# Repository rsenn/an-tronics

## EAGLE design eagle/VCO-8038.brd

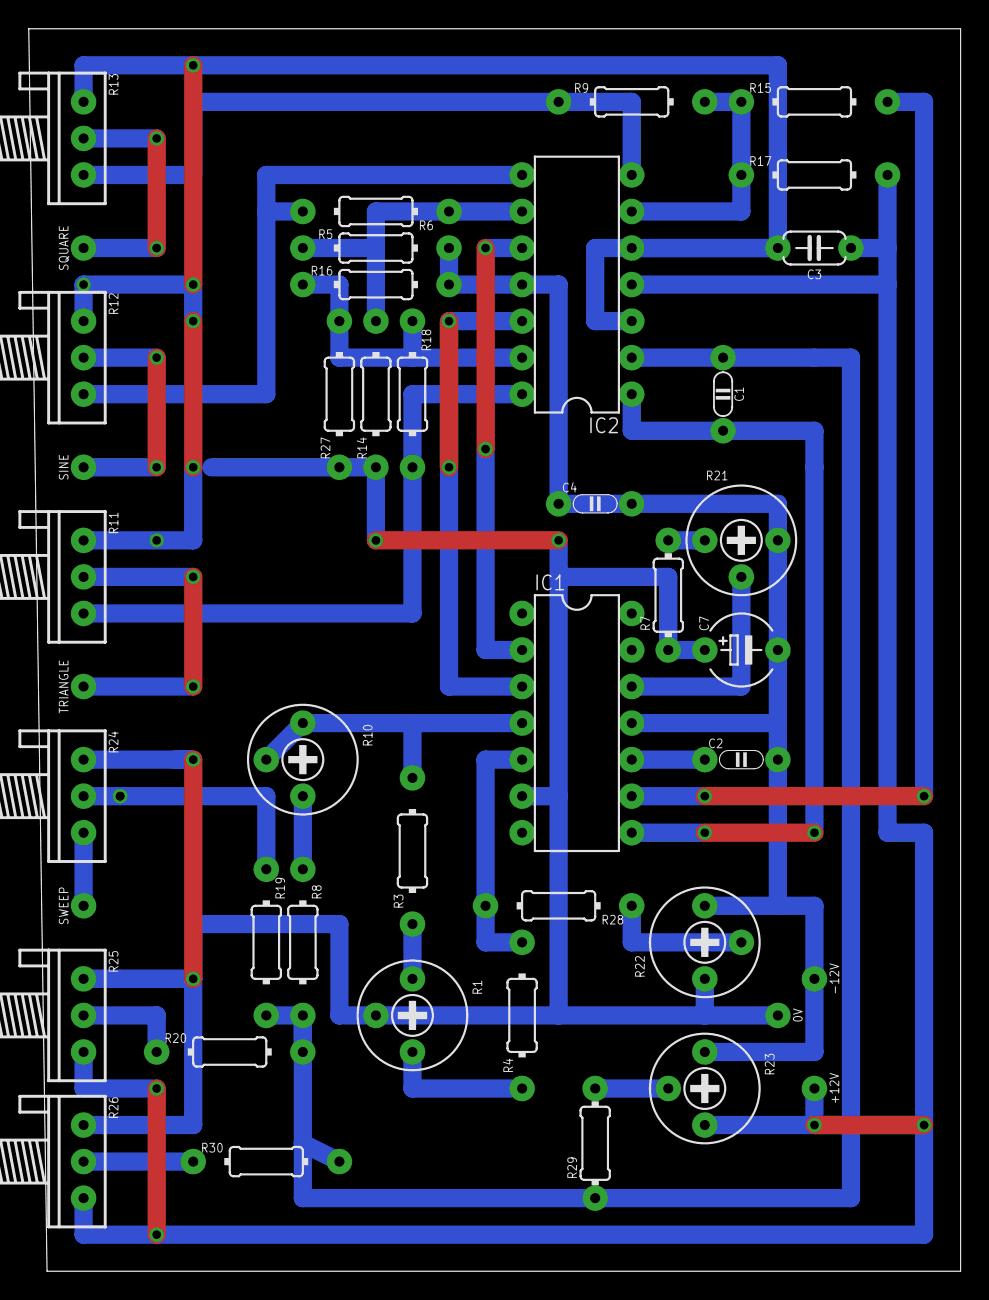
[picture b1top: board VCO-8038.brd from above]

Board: 2 copper layers, 64.8 x 86.4 mm, 43 parts (0 on the bottom side), 31 nets.

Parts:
0V: SPAD
+12V: SPAD
-12V: SPAD
C1: 1nF; C050-020X036/V
C2: 4.7nF; C050-020X036
C3: 10nF; C050-024X044
C4: 10nF; C050-020X036
C7: 4.7μF; E5-5/V
IC1: 8038; DIL14
IC2: TL074_; DIL14
R1: 1kΩ; R-TRIM
R3, R4: 1.5kΩ; 0204/10
R5, R17: 5.6kΩ; 0204/10
R6, R8, R9: 10kΩ; 0204/10
R7: 10kΩ; 0204/7
R10: 10kΩ; R-TRIM
R11, R12, R13: 10kΩ; POT
R14, R15: 12kΩ; 0204/10
R16: 24kΩ; 0204/10
R18: 30kΩ; 0204/10
R19, R20: 100kΩ; 0204/10
R21, R22, R23: 100kΩ; R-TRIM
R24, R25, R26: 100kΩ; POT
R27: 120kΩ; 0204/10
R28: 470kΩ; 0204/10
R29: 10MΩ; 0204/7
R30: 10MΩ; 0204/10
SINE: SPAD
SQUARE: SPAD
SWEEP: SPAD
TRIANGLE: SPAD

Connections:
GND: 0V.1, C3.2, C4.1, C7.+, IC1.6, IC2.3, IC2.5, R1.2, R7.1, R11.A, R12.A, R13.A, R14.1, R22.1, R24.A, R25.A, R26.A, R27.1
LF_SYMM: R22.2, R28.1
unnamed: R23.2, R29.2
unnamed: C1.2, IC1.8, IC2.1
unnamed: C1.1, IC2.2, R8.2, R19.2, R20.2, R29.1, R30.2
unnamed: R26.S, R30.1
unnamed: R20.1, R25.S
unnamed: R19.1, R24.S
unnamed: R24.E, SWEEP.1
unnamed: R8.1, R10.3
unnamed: R1.1, R3.1
unnamed: R1.3, R4.1
unnamed: IC1.4, R3.2, R10.1, R10.2
unnamed: IC2.13, R16.1, R18.1, R27.2
unnamed: IC1.5, R4.2, R28.2
unnamed: IC2.14, R11.E, R18.2
unnamed: R11.S, TRIANGLE.1
unnamed: IC1.3, IC2.12
unnamed: IC2.9, R5.1, R6.1, R14.2
unnamed: IC2.8, R6.2, R12.E
unnamed: R12.S, SINE.1
unnamed: IC1.2, IC2.10
unnamed: R7.2, R21.1
unnamed: IC1.12, R21.2
unnamed: C2.1, IC1.10
unnamed: IC2.6, R9.2, R15.1, R17.1
unnamed: IC2.7, R9.1, R13.E
unnamed: R13.S, SQUARE.1
unnamed: IC1.9, R15.2
V+: +12V.1, C3.1, IC2.4, R17.2, R23.3, R25.E, R26.E
V-: -12V.1, C2.2, C4.2, C7.-, IC1.11, IC2.11, R5.2, R16.2, R21.3, R22.3, R23.1

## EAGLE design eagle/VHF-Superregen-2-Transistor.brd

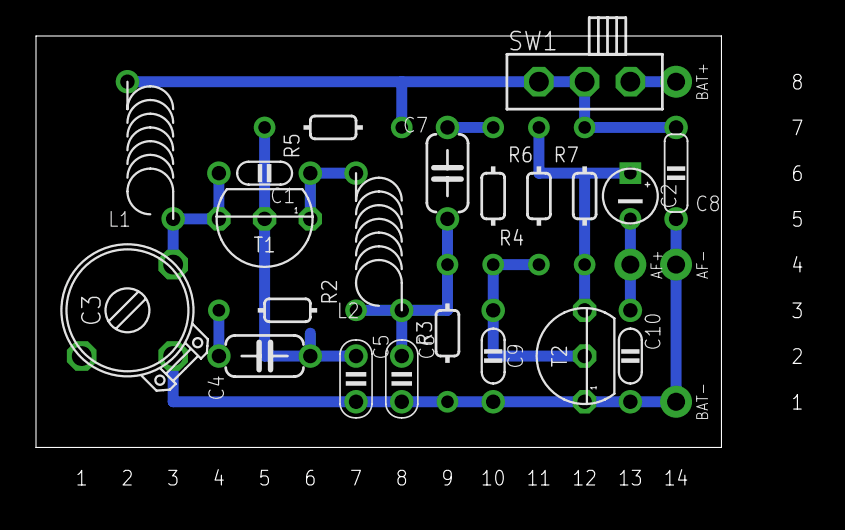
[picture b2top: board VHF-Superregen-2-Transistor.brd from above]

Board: 2 copper layers, 38.1 x 22.9 mm, 25 parts (0 on the bottom side), 12 nets.

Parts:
AF+: SPAD
AF-: SPAD
BAT+: SPAD
BAT-: SPAD
C1: 7p; C050-020X036
C2: 2.2u; E2,5-3
C3: 15p; TRIM-2222-808
C4, C7: 470n; C050-024X044/V
C5, C6: 1n; C025-020X036
C8: 100n; C050-020X044/V
C9: 10n; C050-020X036/V
C10: 47n; C050-020X036
L1, L2: 6; L-04/7V
R2: 12k; 0202/7-V
R3: 10k; 0202/7
R4: 22k; 0202/7-V
R5: 330k; 0202/7-V
R6: 220k; 0202/7-V
R7: 4.7k; 0202/7-V
SW1: SL-SW-1P-2T-H; SLSW-1P2T-H
T1, T2: 2N3904; TO92

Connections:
GND: AF-.1, BAT-.1, C3.2, C5.2, C6.2, C8.2, C9.2, C10.2, R3.2, T2.1
unnamed: C1.2, C3.3, L1.1, T1.3
unnamed: C1.1, L2.2, T1.1
unnamed: C7.1, R4.1
unnamed: C4.2, C5.1, R5.2, T1.2
unnamed: C2.+, R6.2, R7.1, T2.3
unnamed: C6.1, C7.2, L2.1, R2.2, R3.1
unnamed: C4.1, R2.1
unnamed: BAT+.1, SW1.1
unnamed: C9.1, R4.2, R6.1, T2.2
unnamed: AF+.1, C2.-, C10.1
VCC: C8.1, L1.2, R5.1, R7.2, SW1.3

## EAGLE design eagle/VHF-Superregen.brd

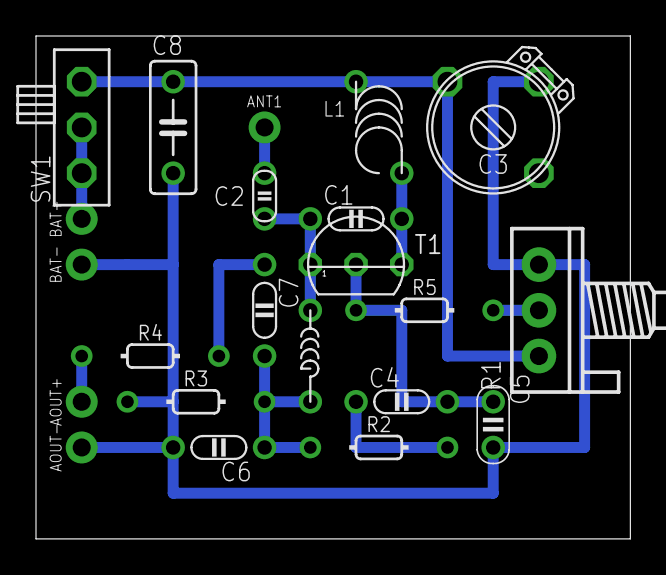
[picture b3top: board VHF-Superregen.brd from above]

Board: 2 copper layers, 33.0 x 27.9 mm, 22 parts (0 on the bottom side), 12 nets.

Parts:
ANT1: ANT; SPAD
AOUT+: SPAD
AOUT-: SPAD
BAT+: SPAD
BAT-: SPAD
C1: 6p; C050-020X036
C2: 2p; C025-015X024
C3: 15 - 140p; TRIM-2222-808
C4, C7: 470n; C050-020X036
C5: 1n; C025-020X036
C6: 1n; C050-020X036
C8: C050-025X075
L1: 6turns on d=0.7mm; L-04-5/5V
L2: L-SHORT02/5; L-02/5V
R1: 47k; POT
R2, R3: 12k; 0202/7
R4: 22k; 0202/7
R5: 68; 0202/7
SW1: SL-SW-1P-2T-H; SLSW-1P2T-H
T1: 2N3904; TO92

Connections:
GND: AOUT-.1, BAT-.1, C3.2, C5.2, C6.2, C8.2, R1.3, R3.2
unnamed: C1.2, L1.2, T1.3
unnamed: C1.1, C2.2, L2.1, T1.1
unnamed: C3.3, C8.1, L1.1, R1.1, SW1.1
unnamed: C4.2, C5.1, R5.2, T1.2
unnamed: ANT1.1, C2.1
unnamed: C4.1, R2.1
unnamed: C7.1, R4.1
unnamed: BAT+.1, SW1.2, SW1.3
unnamed: AOUT+.1, R4.2
unnamed: R1.2, R5.1
unnamed: C6.1, C7.2, L2.2, R2.2, R3.1

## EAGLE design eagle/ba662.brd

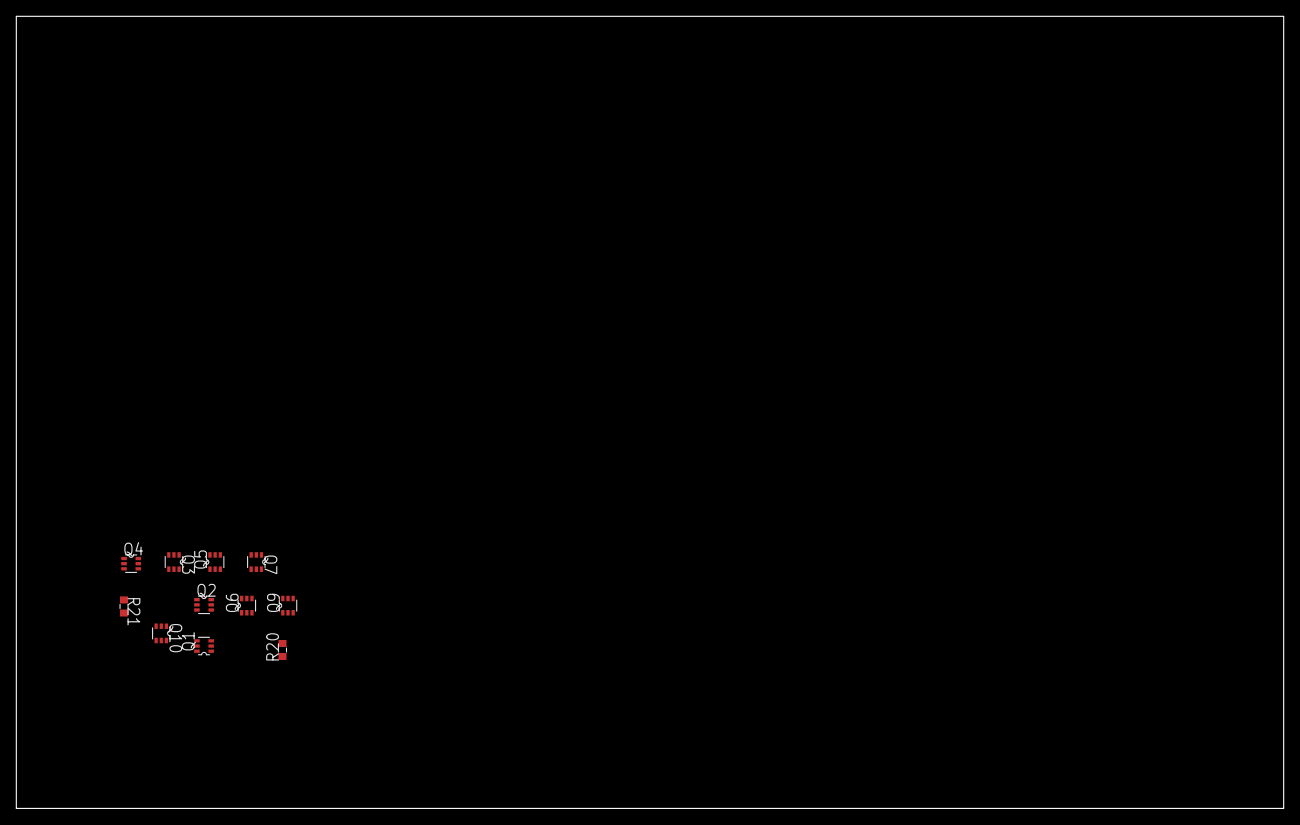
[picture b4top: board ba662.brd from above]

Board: 2 copper layers, 160.0 x 100.0 mm, 11 parts (0 on the bottom side), 14 nets, no tracks yet.

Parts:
Q1: SOT363
Q2, Q3, Q4, Q5, Q6, Q7, Q9, Q10: SOT363; SOT363_Q10
R20: 50kΩ; 0603-SM
R21: 11kΩ; 0603-SM

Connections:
unnamed: Q1.P$4, Q1.P$5, Q6.P$4, Q6.P$5, Q9.P$4, Q9.P$5, Q10.P$6
unnamed: Q1.P$1, Q1.P$2, Q1.P$6
unnamed: Q1.P$3, Q2.P$4, Q2.P$5
unnamed: Q4.P$1, Q4.P$2, Q4.P$3, Q5.P$5
unnamed: Q3.P$1, Q3.P$2, Q3.P$3, Q5.P$4
unnamed: Q2.P$3, Q4.P$6, Q5.P$1
unnamed: Q6.P$1, Q6.P$2, Q6.P$3, Q7.P$4
unnamed: Q5.P$6, Q7.P$3
unnamed: Q2.P$6, Q3.P$6, Q5.P$2
unnamed: Q5.P$3, Q6.P$6, Q7.P$2
unnamed: Q9.P$1, Q9.P$2, Q9.P$3, R20.P$2
unnamed: Q7.P$5, Q9.P$6, Q10.P$1
unnamed: Q10.P$5, R21.P$2
V+: Q3.P$4, Q3.P$5, Q4.P$4, Q4.P$5, Q7.P$6, R21.P$1

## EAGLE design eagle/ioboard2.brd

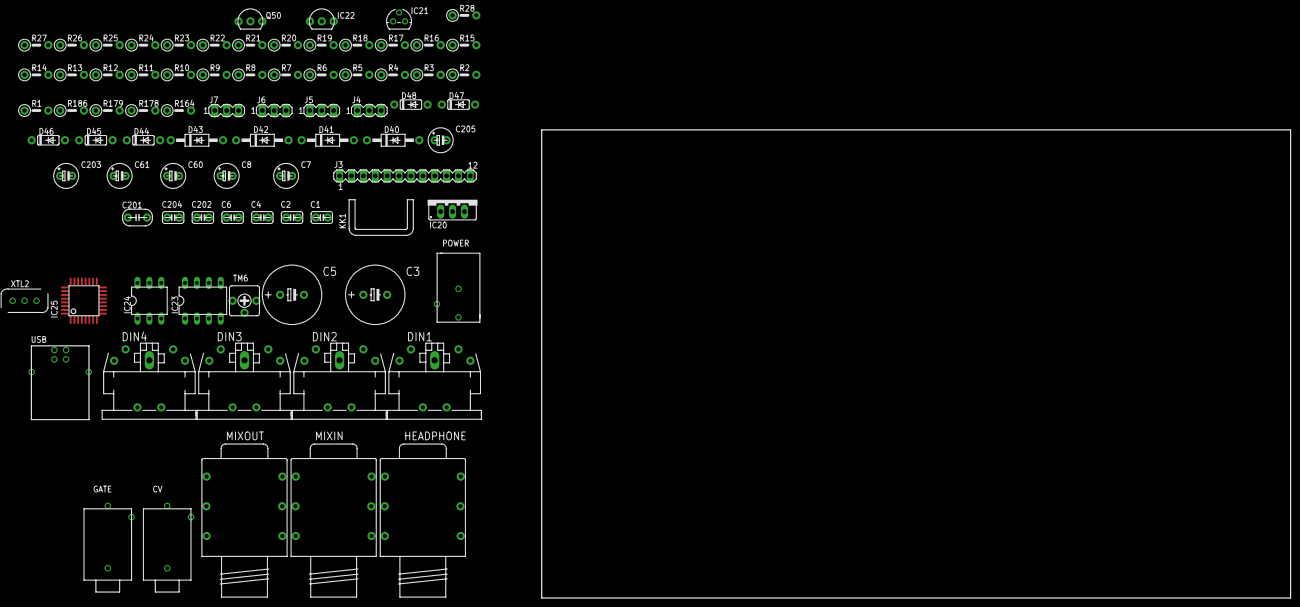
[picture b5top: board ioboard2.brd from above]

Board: 2 copper layers, 160.0 x 100.0 mm, 82 parts (0 on the bottom side), 59 nets, no tracks yet.

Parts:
C1, C2, C4, C6: .1; C050H075X075
C3, C5: 2200/16; E5-13
C7, C8: 100/25; E5-6
C60, C61: 10/16; E5-6
C201: 33nF; C050-025X075
C202, C204: .1μF; C050H075X075
C203, C205: 10μF; E5-6
CV: MONO_CC; CP-3502
D40, D41, D42, D43: 1N4001; DO41-10
D44, D45, D46, D47, D48: 1N4148; DO35-10
DIN1, DIN2, DIN3, DIN4: CP2350; CP-2350
GATE: MONO_CC; CP-3502
HEADPHONE: NEUTRIX_STEREO; REAN_1/4STERO
IC20: 7805; 78XXS
IC21: 78L06Z; TO92
IC22: LM336Z-5.0; 2SC536F
IC23: AN6562; DIL08
IC24: 4N37; DIL06
IC25: FT232; SQFP-S-7X7-32
J3: MA12-1
J4, J5, J6, J7: MA03-1
KK1: D03S
MIXIN: NEUTRIX_STEREO; REAN_1/4STERO
MIXOUT: NEUTRIX_STEREO; REAN_1/4STERO
POWER: 2.1MMJACK; PJ-102A
Q50: 2SC536F
R1, R16: 100Ω; 0207/5V
R2, R17: 1kΩ; 0207/5V
R3: 6.8kΩ; 0207/5V
R4: 5.6kΩ; 0207/5V
R5: 2.4kΩ; 0207/5V
R6, R7: 27Ω; 0207/5V
R8: 1.5kΩ; 0207/5V
R9: 4.7kΩ; 0207/5V
R10, R11: 10kΩ; 0207/5V
R12: 470Ω; 0207/5V
R13, R14, R15, R18, R19: 220Ω; 0207/5V
R20: 22Ω; 0207/5V
R21, R22, R23, R24, R178: 2.2kΩ; 0207/5V
R25, R26, R27, R28: 100kΩ; 0207/5V
R164, R186: 10Ω; 0207/5V
R179: 1.8kΩ; 0207/5V
TM6: 2kΩ; 306
USB: PN61729
XTL2: 6.00MHz; ZTT_XTAL

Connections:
+5.333V: C60.+, IC23.3, IC23.6, IC23.7, J4.1
+5V: C6.1, C202.1, C203.+, C205.+, IC20.OUT, IC24.5, IC25.3, IC25.13, IC25.14, IC25.26, J3.3, J3.4, R11.2, R12.1, R14.2, R17.2, R18.2
+6V: C1.1, IC21.1, J5.3
+12V: C61.+, IC23.1, J4.3, R178.1
DINSYNC1: J3.12, R24.1, R25.2
DINSYNC2: J3.11, R23.2, R26.1
DINSYNC3: J3.10, R22.1, R27.1
DINSYNC4: J3.9, R21.2, R28.2
GND: C1.2, C2.2, C3.-, C4.2, C6.2, C7.-, C8.-, C60.-, C61.-, C201.2, C202.2, C203.-, C204.2, C205.-, CV.SLEEVE, D40.A, D41.A, D44.C, DIN1.2, DIN1.PE, DIN1.PE@, DIN2.2, DIN2.PE, DIN2.PE@, GATE.SLEEVE, HEADPHONE.S, IC20.GND, IC21.2, IC22.3, IC23.4, IC25.9, IC25.17, IC25.29, IC25.31, J3.7, J3.8, J4.2, J5.2, J6.2, J7.2, MIXIN.S, MIXIN.TN, MIXOUT.S, Q50.3, R10.1, R16.1, R20.2, R25.1, R26.2, R27.2, R28.1, R179.2, USB.4, USB.M2, USB.P$2, XTL2.P$2
HP_OUT: J5.1, R164.1, R186.1
MIDI_IN: J3.5, Q50.2, R15.2, R17.1
MIDI_OUT: J3.6, R13.1
unnamed: J7.1, MIXOUT.T
unnamed: J7.3, MIXIN.T
unnamed: C8.+, IC23.8, R1.1
unnamed: D47.A, IC22.2, IC23.5, R3.2
unnamed: IC23.2, R178.2, R179.1
unnamed: C7.+, R2.2, R3.1
unnamed: R4.1, TM6.3
unnamed: R5.2, TM6.1
unnamed: D46.A, D47.C
unnamed: D46.C, R4.2
unnamed: D45.A, R5.1
unnamed: D44.A, D45.C
unnamed: IC22.1, TM6.2
unnamed: R9.1, USB.1
unnamed: D41.C, D42.A, POWER.P$1
unnamed: C5.+, D42.C, D43.C, R1.2, R2.1
unnamed: C2.1, C3.+, C4.1, C5.-, D40.C, D43.A, IC20.IN, IC21.3, POWER.P$2
unnamed: IC24.4, Q50.1, R16.2
unnamed: IC25.27, XTL2.P$1
unnamed: IC25.28, XTL2.P$3
unnamed: IC25.4, R9.2, R10.2
unnamed: DIN4.3, R21.1
unnamed: DIN4.5, R22.2
unnamed: DIN4.1, R24.2
unnamed: DIN4.4, R23.1
unnamed: GATE.TIP, J6.3
unnamed: CV.TIP, J6.1
unnamed: HEADPHONE.R, R164.2
unnamed: HEADPHONE.T, R186.2
unnamed: DIN4.2, R20.1
unnamed: D48.A, DIN3.5, IC24.2
unnamed: D48.C, IC24.1, R19.2
unnamed: DIN3.4, R19.1
unnamed: DIN2.5, R15.1
unnamed: DIN2.4, R18.1
unnamed: DIN1.5, R13.2
unnamed: DIN1.4, R14.1
unnamed: R6.2, USB.2
unnamed: R7.1, USB.3
unnamed: IC25.7, R7.2, R8.2
unnamed: IC25.8, R6.1
unnamed: IC25.5, R8.1
unnamed: C201.1, IC25.6
unnamed: C204.1, IC25.30, R12.2
unnamed: IC25.2, R11.1
USB_RX: IC25.24, J3.2
USB_TX: IC25.25, J3.1

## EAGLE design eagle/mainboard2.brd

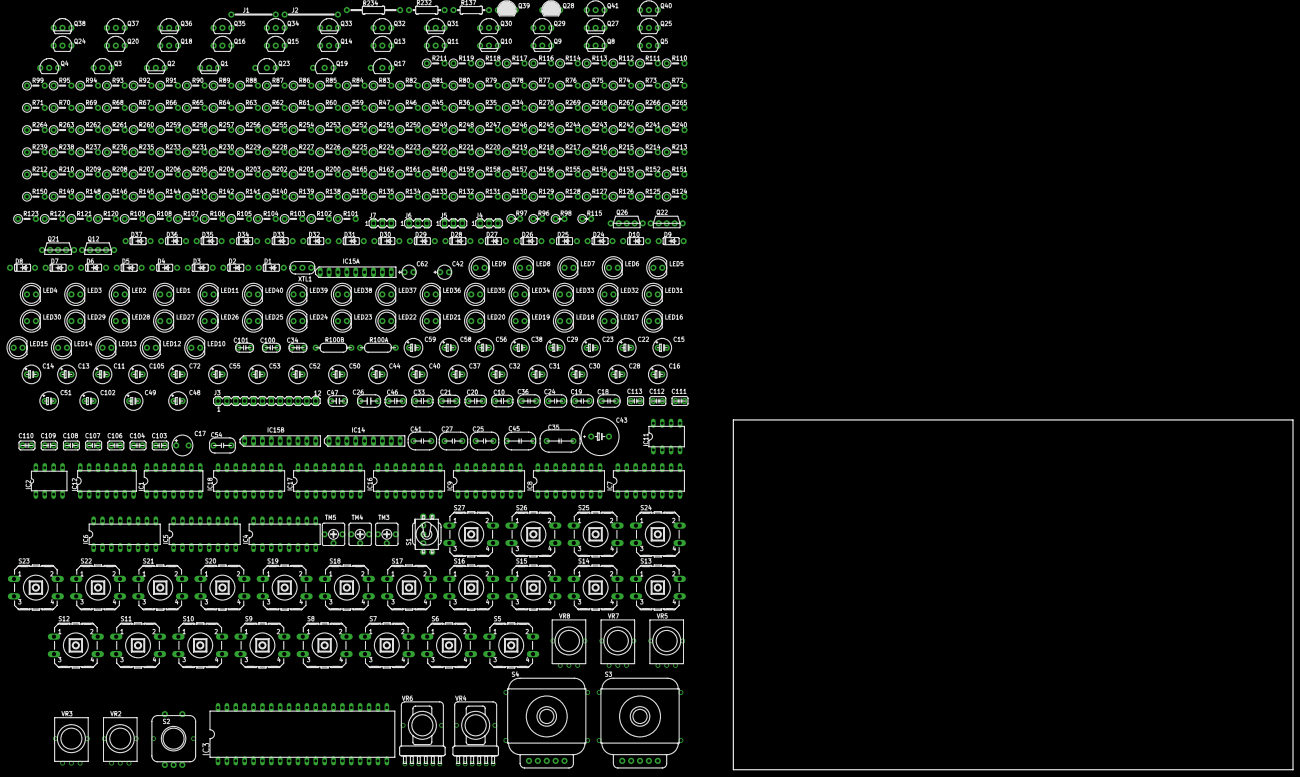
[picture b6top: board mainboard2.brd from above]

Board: 2 copper layers, 160.0 x 100.0 mm, 410 parts (0 on the bottom side), 324 nets, no tracks yet.

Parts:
C10, C20, C21, C33, C46: .01; C050-024X044
C11, C13, C14, C15, C22, C23, C29, C38, C56, C58, C59, C105: 1/50; E5-6
C16, C30, C31, C32, C37, C40, C50, C52, C72: 10/16; E5-6
C17: 1/50; E3,5-8
C18: .018; C050-025X075
C19, C24, C36: .033; C050-025X075
C25, C27, C41: .1; C050-030X075
C26: .033; C075-032X103
C28, C44, C53, C55: 47/16; E5-6
C34, C100, C101: .001; C050-035X075
C35: .22; C050-045X075
C42, C62: 1/35; E2,5-7
C43: 1000/6.3; E5-5
C45: .068; C050-050X075
C47: .0068; C050-075X075
C48, C49: 100/6.3; E5-6
C51: 2.2/50; E5-6
C54: .047; C050-055X075
C102: 100/10; E5-6
C103, C104, C106, C107, C108, C109, C110, C111, C112, C113: .1; C050H075X075
D1, D2, D3, D4, D5, D6, D7, D8, D9, D10, D24, D25, D26, D27, D28, D29, D30, D31, D32, D33, D34, D35, D36, D37: 1N4148; DO35-10
IC1: 74126N; DIL14
IC2: AT25P; DIL08
IC3: MEGA162P; DIL40
IC4, IC5, IC6, IC7, IC8: 74HC595N; DIL16
IC9: 4174P; DIL16
IC11: AN6562; DIL08
IC12: 4066N; DIL14
IC14: LA44140; SIP9
IC15A: BA662; SIP9
IC15B: BA6110; SIP9
IC16, IC17, IC18: 74HC165N; DIL16
J1: J12MM; 12
J2: J15MM; 15
J3: MA12-1
J4, J5, J6, J7: MA03-1
LED1, LED2, LED3, LED4, LED5, LED6, LED7, LED8, LED9, LED10, LED11, LED12, LED13, LED14, LED15, LED16, LED17, LED18, LED19, LED20, LED21, LED22, LED23, LED24, LED25, LED26, LED27, LED28, LED29, LED30, LED31, LED32, LED33, LED34, LED35, LED36, LED37, LED38, LED39, LED40: LED5MM
Q1, Q2, Q8, Q9, Q10, Q27, Q31, Q33, Q36, Q38: 2SA733P; TO92
Q3, Q4, Q5, Q11, Q13, Q14, Q15, Q16, Q18, Q20, Q24, Q25, Q29, Q30, Q32, Q34, Q35, Q37, Q40, Q41: 2SC536F
Q12, Q21, Q26: 2SC1583; SSIP5
Q17, Q19, Q23: 2SC536F; 2SC536_UNEVEN
Q22: 2SC2291; SSIP5
Q28, Q39: 2SK30
R34, R36, R47, R61, R64, R65, R94, R101, R105, R109, R112, R116, R142, R143, R144, R145, R148, R149, R157, R158, R160, R201, R202, R203, R204, R205, R206, R207, R208, R209, R210, R211, R212, R213, R214, R215, R216, R217, R218, R219, R220, R221, R222, R223, R224, R225, R226, R227, R228, R229, R230, R231, R233, R237, R238, R239, R240, R241, R242, R243, R244, R245, R246, R247, R248, R249, R250, R251, R252, R253, R254, R255, R256, R257, R258, R259, R260, R261, R262, R263, R264, R265, R266, R267, R268, R269, R270: 10kΩ; 0207/5V
R35, R59, R66, R72, R73, R92, R93, R99, R102, R113, R114, R118, R122, R139, R140, R141, R153, R154, R156, R165: 100kΩ; 0207/5V
R45, R60, R110, R111, R117, R120, R129, R134, R146, R151: 22kΩ; 0207/5V
R46, R119, R127, R155: 47kΩ; 0207/5V
R62, R63, R103, R121, R128, R131, R235, R236: 220kΩ; 0207/5V
R67, R68, R69, R70, R71, R104, R107, R108, R124, R125, R126, R133, R162: 2.2kΩ; 0207/5V
R74, R75, R76, R77, R78, R79, R80, R81, R82, R83, R84, R85, R86, R87, R88, R89, R90: 200kΩ; 0207/5V
R91, R200: 1MΩ; 0207/5V
R95, R130, R132, R136, R152: 100Ω; 0207/5V
R96, R97, R115: 10kΩ; 0207/2V
R98: 2.2kΩ; 0207/2V
R100A: 3500ppm/C; R-7,5
R100B: 1kΩ; R-7,5
R106: 27kΩ; 0207/5V
R123: 1.5MΩ; 0207/5V
R135: 4.7kΩ; 0207/5V
R137: 1kΩ; 0207/10
R138: 68kΩ; 0207/5V
R150: 22Ω; 0207/5V
R159: 33kΩ; 0207/5V
R161: 1kΩ; 0207/5V
R232: 10kΩ; 0207/10
R234: 10kΩ; 0207/15
S1: SWITCH_GND; NKKTOGGLE
S2: PEC11-S
S3, S4: GH3074
S5, S6, S7, S8, S9, S10, S11, S12, S13, S14, S15, S16, S17, S18, S19, S20, S21, S22, S23, S24, S25, S26, S27: B3F-40XX
TM3: 500K(B); 306
TM4: 50K(B); 306
TM5: 5K(B); 306
VR2, VR7: 50K(B); EVU
VR3, VR5, VR8: 50K(A); EVU
VR4: 50K(B); ALPHADUAL
VR6: 1M(A); ALPHADUAL
XTL1: 16MHZ; 2SC2021

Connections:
+5.333V: C31.+, IC9.1, IC9.16, IC11.3, J4.1, Q26.1, R36.2, R65.2, R66.2, R68.1, R78.1, R100A.2, R100B.1, R101.2, R116.2, R117.1, R126.1, R157.2, R162.1, TM4.3, VR2.3
+5V: C102.+, C103.1, C104.2, C106.2, C107.2, C108.2, C109.2, C110.2, C111.2, C112.2, C113.2, D1.C, IC1.1, IC1.14, IC2.3, IC2.7, IC2.8, IC3.40, IC4.10, IC4.16, IC5.10, IC5.16, IC6.10, IC6.16, IC7.10, IC7.16, IC8.10, IC8.16, IC16.16, IC17.16, IC18.16, J2.2, J3.3, J3.4, R200.1, S5.2, S6.3, S7.1, S8.1, S9.1, S10.1, S11.1, S12.4, S13.4, S14.2, S15.4, S16.4, S17.2, S18.2, S19.1, S19.2, S20.2, S21.2, S22.1, S22.2, S23.1, S23.2, S24.2, S25.4, S26.4, S27.2
+6V: C46.1, C49.+, D33.C, IC14.7, J5.3
+12V: C32.+, C72.+, D31.C, IC11.8, IC12.14, IC15A.4, IC15A.9, IC15B.9, J4.3, Q1.3, Q2.3, Q27.3, Q28.1, Q36.3, Q40.2, Q41.2, R45.1, R92.2, R93.1, R95.2, R103.1, R123.2, R136.1, R139.2, R142.2, R149.2, R150.1, TM4.1, VR3.3
ACCENT: IC3.28, R141.2
C48: C48.+, IC14.9
DINSYNC1: IC3.17, J3.12
DINSYNC2: IC3.16, J3.11
DINSYNC3: IC3.15, J3.10
DINSYNC4: IC3.14, J3.9
GATE: IC3.30, R146.2
GND: C11.-, C13.-, C16.-, C22.-, C28.-, C29.-, C30.-, C31.-, C32.-, C33.2, C35.2, C36.2, C37.-, C40.-, C41.2, C42.-, C45.2, C48.-, C49.-, C52.-, C53.-, C55.-, C62.-, C100.1, C101.1, C102.-, C103.2, C104.1, C105.-, C106.1, C107.1, C108.1, C109.1, C110.1, C111.1, C112.1, C113.1, D26.C, D30.A, D32.A, IC1.4, IC1.5, IC1.7, IC1.12, IC1.13, IC2.4, IC3.20, IC4.8, IC4.13, IC5.8, IC5.13, IC6.8, IC6.13, IC7.8, IC7.13, IC8.8, IC8.13, IC9.8, IC11.4, IC12.7, IC14.5, IC15A.5, IC15B.3, IC15B.5, IC16.8, IC16.10, IC16.15, IC17.8, IC17.15, IC18.8, IC18.15, J3.7, J3.8, J4.2, J5.2, J6.2, J7.2, LED1.K, LED2.K, LED3.K, LED4.K, LED5.K, LED6.K, LED7.K, LED8.K, LED9.K, LED10.K, LED11.K, LED12.K, LED13.K, LED14.K, LED15.K, LED16.K, LED17.K, LED18.K, LED19.K, LED20.K, LED21.K, LED22.K, LED23.K, LED24.K, LED25.K, LED26.K, LED27.K, LED28.K, LED29.K, LED30.K, LED31.K, LED32.K, LED33.K, LED34.K, LED35.K, LED36.K, LED37.K, LED38.K, LED39.K, LED40.K, Q3.3, Q4.3, Q5.3, Q9.2, Q29.3, Q30.3, Q35.3, Q37.3, Q39.2, Q39.3, R60.1, R64.2, R94.1, R96.1, R105.1, R108.1, R109.2, R130.2, R135.1, R140.2, R144.2, R145.1, R151.1, R160.1, R165.2, R201.2, R202.2, R206.2, R207.1, R209.2, R210.2, R212.2, R214.2, R216.2, R218.2, R219.2, R220.2, R224.2, R225.2, R226.2, R230.2, R231.2, R232.2, R233.2, R240.2, R247.2, R255.1, R257.2, R259.2, R263.2, S1.M1, S1.M2, S1.M3, S1.M4, S2.C, S2.P$1, S2.P$2, S3.MT1, S3.MT2, S3.MT3, S3.MT4, S4.MT1, S4.MT2, S4.MT3, S4.MT4, VR2.1, VR2.M1, VR2.M2, VR3.M1, VR3.M2, VR4.1A, VR4.M1, VR4.M2, VR5.M1, VR5.M2, VR6.1A, VR6.2A, VR6.3A, VR6.M1, VR6.M2, VR7.1, VR7.M1, VR7.M2, VR8.1, VR8.M1, VR8.M2, XTL1.2
LED_LATCH: IC3.32, IC4.12, IC5.12, IC6.12, IC7.12, IC8.12
MIDI_IN: IC3.10, J3.5
MIDI_OUT: IC3.11, J3.6
unnamed: C51.-, IC14.2
unnamed: C51.+, R159.1
unnamed: C50.+, IC14.3
unnamed: C50.-, R135.2
unnamed: Q34.3, R153.1, R155.2, R156.1
unnamed: C56.+, R161.1
unnamed: C56.-, J7.1, R165.1
unnamed: C47.1, IC14.4
unnamed: C47.2, IC14.1
unnamed: C43.-, J5.1
unnamed: C43.+, C44.-, C45.1, D32.C, D33.A, IC14.6
unnamed: Q33.2, R153.2, R159.2, R160.2, R161.2
unnamed: C44.+, C46.2, IC14.8
unnamed: Q34.2, R154.1, R158.1
unnamed: Q33.1, R158.2
unnamed: C53.+, Q33.3, R136.2, R154.2
unnamed: C52.+, Q34.1, R157.1
unnamed: C59.+, R155.1
unnamed: C58.+, R156.2
unnamed: C58.-, J7.3
unnamed: C20.1, R122.2
unnamed: C37.+, R124.2, R125.1, R126.2
unnamed: IC7.1, R252.2
unnamed: IC15A.2, IC15B.2, R125.2
unnamed: C21.1, R121.1
unnamed: C15.-, C20.2, VR4.2A
unnamed: C14.-, C21.2, VR4.3A
unnamed: IC15A.6, IC15A.7, IC15B.6, IC15B.7, R127.1, R128.2
unnamed: IC15B.4, Q1.2
unnamed: R127.2, R129.1
unnamed: C40.+, R128.1, R129.2, R162.2
unnamed: C38.-, VR8.3
unnamed: D27.A, R120.1
unnamed: C36.1, R119.1, R120.2
unnamed: D24.A, R119.2, VR7.2
unnamed: C55.+, Q38.3, R150.2
unnamed: C72.-, Q36.1, R142.1, R143.2
unnamed: D34.A, D35.A, Q36.2, R145.2
unnamed: Q38.1, R148.2, R149.1
unnamed: D37.C, R152.2
unnamed: C54.1, R148.1
unnamed: C54.2, Q37.2, R143.1
unnamed: Q37.1, R144.1, R146.1
unnamed: D36.A, D37.A, Q38.2, R151.2
unnamed: C62.+, Q40.1, R138.2, R152.1
unnamed: Q40.3, Q41.1
unnamed: C38.+, IC15A.8, IC15B.8
unnamed: R61.1, VR5.1
unnamed: D26.A, D29.C, R117.2
unnamed: D28.C, D29.A
unnamed: D28.A, IC12.4, VR6.2B, VR6.3B
unnamed: IC12.1, Q39.1, Q41.3, VR5.3
unnamed: Q35.1, R140.1, R141.1
unnamed: Q32.3, R130.1
unnamed: IC12.5, IC12.13, Q35.2, R139.1
unnamed: D34.C, R137.1
unnamed: Q5.1, R254.1, R255.2
unnamed: Q12.5, R97.1, R98.1
unnamed: D35.C, R133.2
unnamed: D36.C, R134.1
unnamed: C41.1, Q32.1, R134.2
unnamed: Q32.2, R132.2
unnamed: C42.+, Q31.1, R123.1, R132.1
unnamed: D27.C, IC15A.1, Q3.1, Q3.2, Q4.1, Q31.2
unnamed: Q31.3, R131.1
unnamed: R131.2, R133.1
unnamed: IC9.10, R90.1
unnamed: R236.1, R269.2, S2.B
unnamed: IC4.7, R241.1
unnamed: C35.1, IC12.9, IC12.10
unnamed: IC12.6, Q30.2, R93.2
unnamed: Q30.1, R91.2
unnamed: IC11.6, R107.1
unnamed: R85.2, R86.1, R87.2, R88.2, R89.1
unnamed: IC1.9, IC18.9
unnamed: IC12.12, Q29.2, R91.1, R92.1
unnamed: R79.1, R83.1, R84.2, R85.1, R86.2
unnamed: C105.+, D1.A, D2.C, IC1.2, R200.2
unnamed: IC9.15, R81.2
unnamed: IC9.2, R82.1
unnamed: IC9.12, R79.2
unnamed: Q29.1, R59.2, R60.2
unnamed: C34.1, IC11.1, R104.2
unnamed: C34.2, IC11.2, Q26.2, R102.1, R103.2
unnamed: Q26.5, R100A.1, R100B.2, R106.2, R118.2
unnamed: IC4.6, R237.1
unnamed: Q26.3, R104.1
unnamed: R118.1, VR2.2
unnamed: D25.A, Q27.2
unnamed: D25.C, Q24.1, Q24.2, Q25.1
unnamed: Q24.3, R101.1
unnamed: Q25.2, Q27.1
unnamed: IC17.5, R207.2, S12.1
unnamed: C10.1, Q28.3, R35.1, R105.2, S1.1
unnamed: Q8.1, R34.1, R35.2
unnamed: C10.2, R34.2
unnamed: IC11.5, IC12.8, R88.1, R89.2, R90.2
unnamed: C33.1, Q25.3, Q26.4, Q28.2
unnamed: R102.2, TM4.2
unnamed: C30.+, Q22.3, R115.2
unnamed: C24.1, Q14.1, Q14.2, Q16.3
unnamed: C19.1, Q13.1, Q13.2, Q14.3
unnamed: C18.2, Q12.2, Q13.3
unnamed: C24.2, Q17.1, Q17.2, Q23.3
unnamed: C26.2, C27.1, Q22.5, Q23.1, Q23.2
unnamed: C18.1, Q12.4, Q15.3
unnamed: C28.+, Q18.2, Q19.2, Q22.2, Q22.4, R95.1, R110.2, R111.1, R115.1
unnamed: C17.+, R62.2
unnamed: C17.-, Q12.1, R70.1
unnamed: C16.+, R68.2, R70.2, R98.2
unnamed: R62.1, S1.2
unnamed: Q12.3, R69.1
unnamed: C23.+, R97.2
unnamed: LED6.A, R244.1
unnamed: C23.-, Q18.3, R94.2
unnamed: Q18.1, R67.2, R99.2
unnamed: C22.+, R66.1, R99.1
unnamed: C15.+, R67.1
unnamed: Q10.1, R63.1, R71.2, R72.1
unnamed: Q20.1, R109.1, R112.2
unnamed: Q20.3, R108.2
unnamed: LED7.A, R250.1
unnamed: C25.2, Q21.1, R114.2
unnamed: Q20.2, Q21.3
unnamed: Q19.1, Q21.2, R110.1
unnamed: C27.2, Q21.5, R113.1
unnamed: R47.1, VR3.1
unnamed: C25.1, C26.1, Q16.1, Q16.2, Q22.1
unnamed: C14.+, Q19.3, R96.2
unnamed: Q11.2, R69.2
unnamed: Q10.3, Q11.1, R73.1
unnamed: Q21.4, R111.2
unnamed: Q9.1, R64.1, R65.1
unnamed: IC12.2, VR7.3
unnamed: R73.2, TM3.2, TM3.3
unnamed: R72.2, VR4.2B
unnamed: R63.2, VR5.2
unnamed: TM3.1, VR3.2
unnamed: R76.2, R77.1, R80.2, R83.2, R84.1
unnamed: IC12.3, R138.1, VR6.1B
unnamed: R106.1, TM5.1
unnamed: C59.-, VR8.2
unnamed: D24.C, R46.1
unnamed: R46.2, VR4.1B
unnamed: C13.+, VR4.3B
unnamed: R257.1, S10.4
unnamed: IC17.14, R218.1, S9.3
unnamed: IC17.13, S8.3
unnamed: IC17.12, R225.1, S7.3
unnamed: R259.1, S11.4
unnamed: IC18.14, R230.1, S5.4
unnamed: D3.C, S4.P$1
unnamed: IC18.12, R232.1, S15.1
unnamed: R206.1, S26.2
unnamed: IC16.5, S27.3
unnamed: IC17.9, IC18.10
unnamed: IC18.4, R224.1, S18.4
unnamed: IC17.4, S11.3
unnamed: D4.C, S4.P$2
unnamed: R209.1, S25.2
unnamed: IC4.5, R234.1
unnamed: IC5.9, IC7.14
unnamed: IC5.6, R243.2
unnamed: IC5.7, R244.2
unnamed: IC5.5, R242.1
unnamed: IC7.15, R250.2
unnamed: IC7.2, R251.1
unnamed: LED1.A, R234.2
unnamed: LED2.A, R237.2
unnamed: IC7.3, R253.1
unnamed: IC7.4, R256.1
unnamed: LED14.A, R262.1
unnamed: IC8.3, R264.1
unnamed: IC8.6, R267.1
unnamed: IC8.7, R268.1
unnamed: IC8.5, R266.2
unnamed: IC5.1, R223.1
unnamed: IC8.4, R265.1
unnamed: IC5.2, R222.2
unnamed: IC5.15, R221.1
unnamed: IC5.4, R246.1
unnamed: IC5.3, R245.2
unnamed: IC4.3, R238.2
unnamed: IC4.4, R239.2
unnamed: IC4.1, R229.1
unnamed: IC7.6, R261.1
unnamed: IC7.7, R262.2
unnamed: IC7.5, R260.1
unnamed: IC4.2, R228.2
unnamed: IC4.15, R227.1
unnamed: IC8.15, R203.1
unnamed: IC8.1, R205.1
unnamed: IC8.2, R204.2
unnamed: IC6.15, R208.1
unnamed: IC6.1, R211.1
unnamed: IC6.2, R213.1
unnamed: IC6.3, R215.1
unnamed: IC6.4, R217.2
unnamed: IC6.7, R248.1
unnamed: IC6.6, R249.2
unnamed: IC6.5, R258.1
unnamed: IC16.9, IC17.10
unnamed: IC16.13, R214.1, S22.4
unnamed: R210.1, S24.4
unnamed: IC16.11, S23.3
unnamed: IC16.4, S26.1
unnamed: IC18.6, R219.1, S20.4
unnamed: IC16.12, R216.1, S21.4
unnamed: R240.1, S6.2
unnamed: IC16.14, S24.3
unnamed: IC9.7, R87.1
unnamed: R201.1, S27.4
unnamed: R235.1, R270.1, S2.A
unnamed: R212.1, S23.4
unnamed: IC9.5, R80.1
unnamed: R74.2, R75.2, R78.2, R82.2
unnamed: LED9.A, R252.1
unnamed: LED10.A, R253.2
unnamed: LED11.A, R256.2
unnamed: LED12.A, R260.2
unnamed: IC18.5, R220.1, S19.4
unnamed: R74.1, R75.1, R76.1, R77.2, R81.1
unnamed: R231.1, S16.2
unnamed: IC16.6, R202.1, S14.3
unnamed: R263.1, S13.2
unnamed: Q5.2, S4.C
unnamed: IC17.6, S13.1
unnamed: IC18.3, R226.1, S17.4
unnamed: IC17.3, S10.3
unnamed: LED16.A, R267.2
unnamed: IC17.11, S6.1
unnamed: IC18.11, S16.1
unnamed: IC16.3, S25.1
unnamed: R247.1, S8.4
unnamed: LED3.A, R241.2
unnamed: LED4.A, R242.2
unnamed: LED5.A, R243.1
unnamed: LED15.A, R266.1
unnamed: LED8.A, R251.2
unnamed: LED13.A, R261.2
unnamed: IC4.9, IC5.14
unnamed: IC6.14, IC7.9
unnamed: IC6.9, IC8.14
unnamed: LED17.A, R268.2
unnamed: LED18.A, R238.1
unnamed: LED19.A, R239.1
unnamed: LED20.A, R245.1
unnamed: LED21.A, R246.2
unnamed: LED22.A, R248.2
unnamed: LED23.A, R249.1
unnamed: LED24.A, R258.2
unnamed: LED25.A, R265.2
unnamed: LED26.A, R264.2
unnamed: LED27.A, R203.2
unnamed: LED28.A, R229.2
unnamed: LED29.A, R228.1
unnamed: LED30.A, R227.2
unnamed: LED31.A, R223.2
unnamed: LED32.A, R222.1
unnamed: LED33.A, R221.2
unnamed: LED34.A, R217.1
unnamed: LED35.A, R215.2
unnamed: LED36.A, R213.2
unnamed: LED37.A, R211.2
unnamed: LED38.A, R208.2
unnamed: LED39.A, R205.2
unnamed: LED40.A, R204.1
unnamed: D2.A, IC1.3, IC3.9
unnamed: D5.C, S4.P$4
unnamed: D6.C, S4.P$8
unnamed: D7.C, S3.P$1
unnamed: D8.C, S3.P$2
unnamed: D9.C, S3.P$4
unnamed: D10.C, S3.P$8
unnamed: C11.+, Q8.3, R45.2
unnamed: Q8.2, R36.1, S1.3
unnamed: J1.1, S2.SW1
unnamed: J2.1, R269.1, R270.2, S2.SW2
unnamed: IC3.18, XTL1.3
unnamed: Q9.3, Q10.2, Q11.3, R47.2, R61.2, R71.1
unnamed: C29.+, R112.1, R113.2, R114.1, R116.1
unnamed: Q1.1, Q2.1, Q2.2, Q4.2
unnamed: J6.3, R137.2
unnamed: IC15A.3, IC15B.1, R121.2, R122.1, R124.1
unnamed: D30.C, D31.A, IC11.7, IC12.11, J6.1, R107.2, TM5.2, TM5.3
NOTE0: IC3.21, IC9.3
NOTE1: IC3.22, IC9.14
NOTE2: IC3.23, IC9.4
NOTE3: IC3.24, IC9.13
NOTE4: IC3.25, IC9.6
NOTE5: IC3.26, IC9.11
NOTE_LATCH: IC3.29, IC9.9
Q17: C19.2, Q15.1, Q15.2, Q17.3
ROTARY1: D3.A, D7.A, IC3.34
ROTARY2: D4.A, D8.A, IC3.35
ROTARY4: D5.A, D9.A, IC3.36
ROTARY8: D6.A, D10.A, IC3.37
ROTARYCOM3: IC3.33, R254.2, S3.C
SLIDE: IC3.27, R59.1
SPI_CLK: IC2.6, IC3.8, IC4.11, IC5.11, IC6.11, IC7.11, IC8.11, IC16.2, IC17.2, IC18.2
SPI_IN: IC2.5, IC3.6, IC4.14
SPI_OUT: IC1.8, IC2.2, IC3.7
SWITCH_LATCH: IC1.10, IC2.1, IC3.1, IC16.1, IC17.1, IC18.1
TEMPO_SW: IC18.13, J1.2, R233.1
TEMPO_SW_A: C100.2, IC3.38, R235.2
TEMPO_SW_B: C101.2, IC3.39, R236.2
USBRX: IC3.3, J3.1
USB_TX: IC3.4, J3.2
XTL1: IC3.19, XTL1.1

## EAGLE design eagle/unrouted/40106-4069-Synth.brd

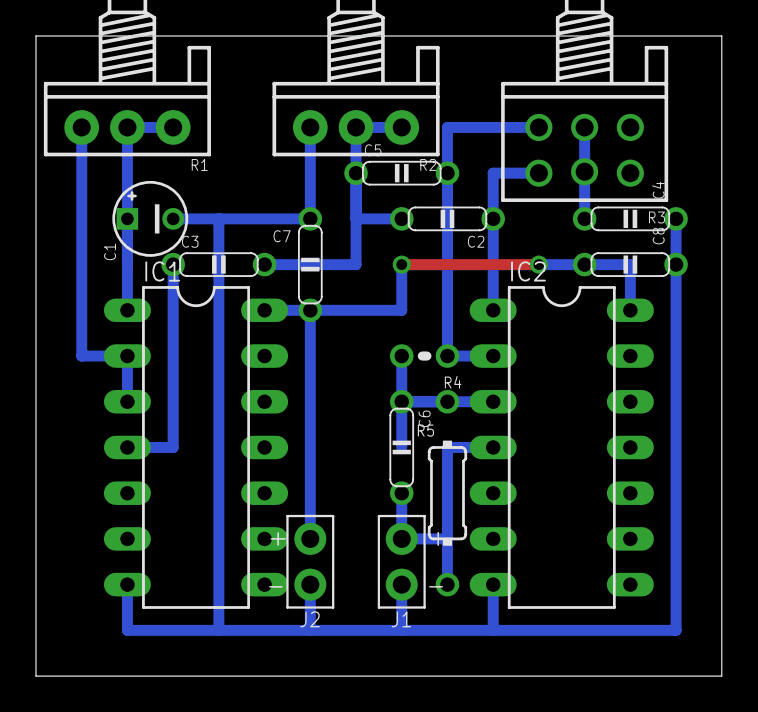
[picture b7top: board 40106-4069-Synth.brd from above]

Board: 2 copper layers, 38.1 x 35.6 mm, 17 parts (0 on the bottom side), 11 nets.

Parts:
C1: 1uF; E2.5-4/V
C2, C3, C5: 100nF; C050-020X044
C4: 220nF; C050-020X044/V
C6: 10nF; C050-020X044
C7, C8: 100nF; C050-020X044/V
IC1: 40106N; DIL14
IC2: 4069N; DIL14
J1: SPAD+-+-; SPAD+-
J2: SPAD-+
R1, R2: 100k; POT
R3: 100k; POT-STEREO-2X3
R4: 0204V
R5: 0204/10-V

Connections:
GND: C1.-, C4.1, C7.1, C8.1, IC1.7, IC2.7, J1.1, J2.1, R2.3
unnamed: C3.1, IC1.4
unnamed: C1.+, IC1.1, R1.1, R1.2
unnamed: IC1.2, IC1.3, R1.3
unnamed: C2.2, C3.2, C5.1, R2.1, R2.2
unnamed: C5.2, IC2.2, R3.1-E, R4.1
unnamed: C2.1, IC2.1, R3.2-E
unnamed: C6.1, IC2.3, R4.2, R5.1
unnamed: C6.2, IC2.4, J1.2, R5.2
unnamed: C4.2, R3.1-S, R3.2-S
VCC: C7.2, C8.2, IC1.14, IC2.14, J2.2
